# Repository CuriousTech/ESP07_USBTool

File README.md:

# ESP07_USBTool
3-in-1 board for ESP-07/12

[Clone from BangGood using spring clips](https://www.banggood.com/ESP8266-Test-Board-Burner-Development-Board-WIFI-Module-For-ESP-01-ESP-01S-ESP-12E-ESP-12F-ESP-12S-ESP-18T-p-1684992.html?rmmds=email_recommend&currency=USD&utm_source=emarsys&utm_medium=mail_automail20_email&utm_campaign=newsletterai&utm_content=leander&sc_src=email_4946888&sc_eh=43f0619848408ee71&sc_llid=1625077&sc_lid=218152908&sc_uid=fY5pSVPcVh&cur_warehouse=CN)

USB powered with FTDI for programming and testing.  
Leave the FTDI and supporting components off for standalone USB 5V powered or 3.5-6V using pads on bottom rear.  
Use as serial+3V3 breakout with 0.1" pads for header on top rear of board.  
  
Rev 1.  Pogo pins are optional.  Outer 4 pinholes are for hold downs and should be done last for adjusting.  Get the height of the outer pins above inner, but only less that the size of the PCB.  
  
deepSleep is the R9 resistor  
run is R10   

For more on the pogo-pins.  Lineup was done using all 3 PCBs and spacers.  Paste on top and heatgun.

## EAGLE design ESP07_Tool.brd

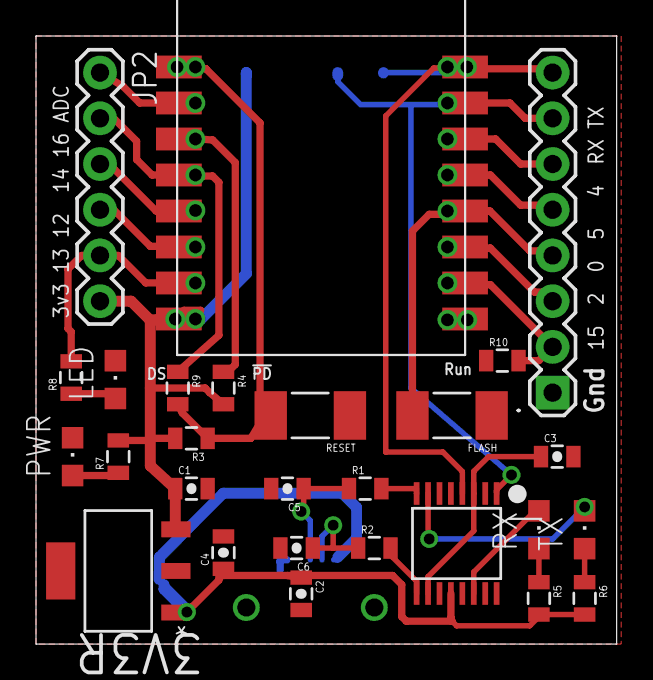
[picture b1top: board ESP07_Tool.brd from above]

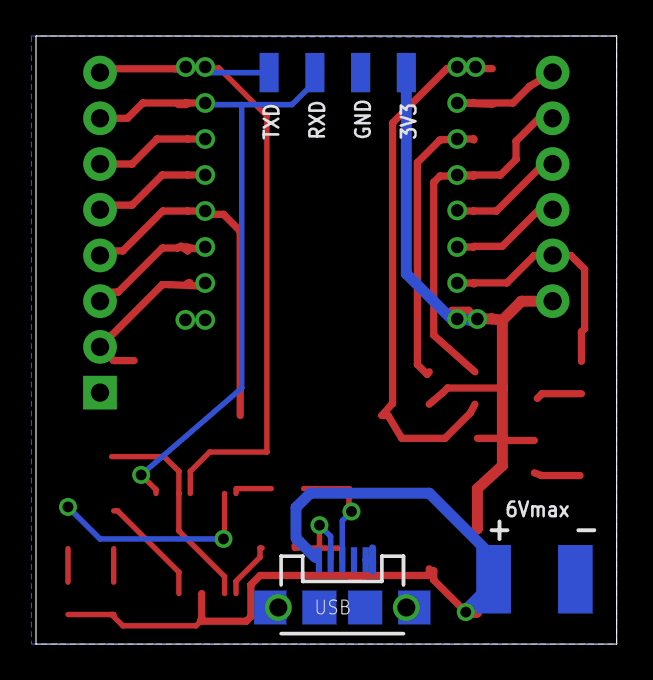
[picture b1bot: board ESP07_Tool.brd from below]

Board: 2 copper layers, 32.3 x 33.8 mm, 34 parts (7 on the bottom side), 28 nets.

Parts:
3V3R: MCP1824ST-3302E/DB; SOT230P700X180-4N
.: 1X08
C1, C2: 1uF; 0805-CAP
C3, C4: 0.1uF; 0805-CAP
C5, C6: 47pF; 0805-CAP
FLASH: R2010
JP2: 1X06
LED: CHIPLED_0805
PWR: CHIPLED_0805
R1, R2: 27; 0805
R3, R4, R9, R10: 10K; 0805
R5, R6, R7, R8: 330; 0805
RESET: R2010
RX: CHIPLED_0805
TX: CHIPLED_0805
U$1: ESP-07/12
U$2, U$3: SMD-PAD-SM; SMD-PAD3
U$4, U$5, U$6, U$7: SMD-PAD1
USB: USB-MICROB
|: IC_FT230X-SSOP-16; SSOP-16-FTDI

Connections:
3V3: 3V3R.3, C1.1, JP2.6, R3.2, R4.2, R7.2, U$1.VCC, U$6.>NAME
GND: 3V3R.2, 3V3R.4, ..1, C1.2, C2.2, C3.2, C4.2, C5.2, C6.2, FLASH.1, LED.C, PWR.C, R10.1, RESET.1, U$1.GND, U$2.P$1, U$7.>NAME, USB.GND, USB.MT1, USB.MT2, |.5, |.13
unnamed: JP2.3, U$1.GPIO14
unnamed: LED.A, R8.1
unnamed: ..6, U$1.GPIO4
unnamed: PWR.A, R7.1
unnamed: C3.1, |.3, |.10
unnamed: TX.C, |.7
unnamed: ..3, U$1.GPIO2
unnamed: ..2, R10.2, U$1.GPIO15
unnamed: ..5, U$1.GPIO5
unnamed: ..4, FLASH.2, U$1.GPIO0
unnamed: R4.1, U$1.CH_PD
unnamed: JP2.1, U$1.ADC
unnamed: RX.C, |.14
unnamed: R5.1, RX.A
unnamed: JP2.2, R9.1, U$1.GPIO16
unnamed: JP2.4, U$1.GPIO12
unnamed: JP2.5, R8.2, U$1.GPIO13
unnamed: R6.1, TX.A
unnamed: R2.2, |.9
unnamed: R1.2, |.8
unnamed: R3.1, R9.2, RESET.2, U$1.REST
unnamed: C6.1, R2.1, USB.D-
unnamed: C5.1, R1.1, USB.D+
RXD: ..7, U$1.RXD, U$4.>NAME, |.1
TXD: ..8, U$1.TXD, U$5.>NAME, |.4
VCC: 3V3R.1, C2.1, C4.1, R5.2, R6.2, U$3.P$1, USB.VBUS, |.12

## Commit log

2015-06-20 Fixed pogo pin positions
2015-06-20 Update for pogo changes
2015-06-20 Moved pads in 13mm wide
2015-06-20 Update just in case
2015-06-21 Mods after actual use
2015-06-21 Sync with .brd
2015-06-21 New pic
2015-06-22 Added 3v3 and gnd header pins
2015-06-24 Switched to MCP1824ST-3302E/DB
2015-06-24 New LDO
2015-07-04 Added more regulator options
2015-07-08 Rev 1 pics

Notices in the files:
parts and their libraries:
SparkFun-Connectors: Licensing: Creative Commons ShareAlike 4.0 International - https://creativecommons.org/licenses/by-sa/4.0
